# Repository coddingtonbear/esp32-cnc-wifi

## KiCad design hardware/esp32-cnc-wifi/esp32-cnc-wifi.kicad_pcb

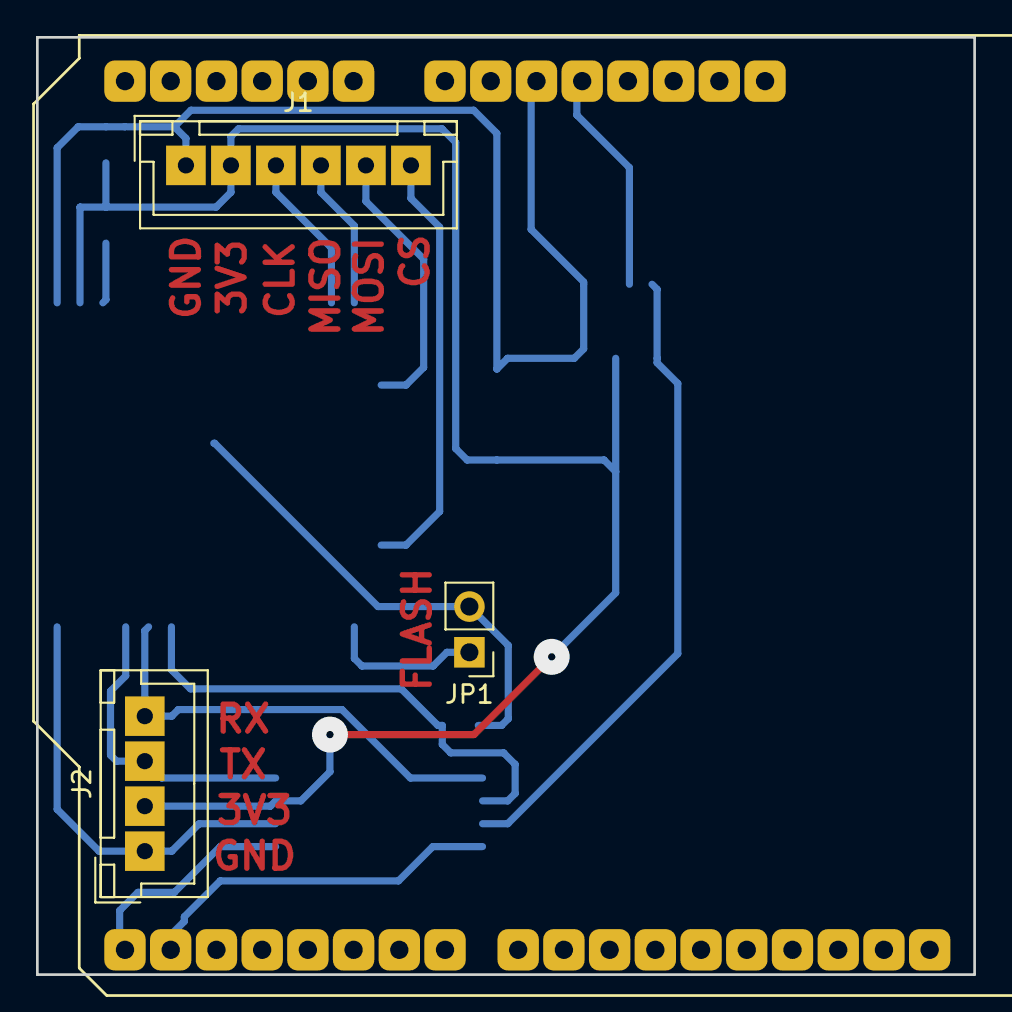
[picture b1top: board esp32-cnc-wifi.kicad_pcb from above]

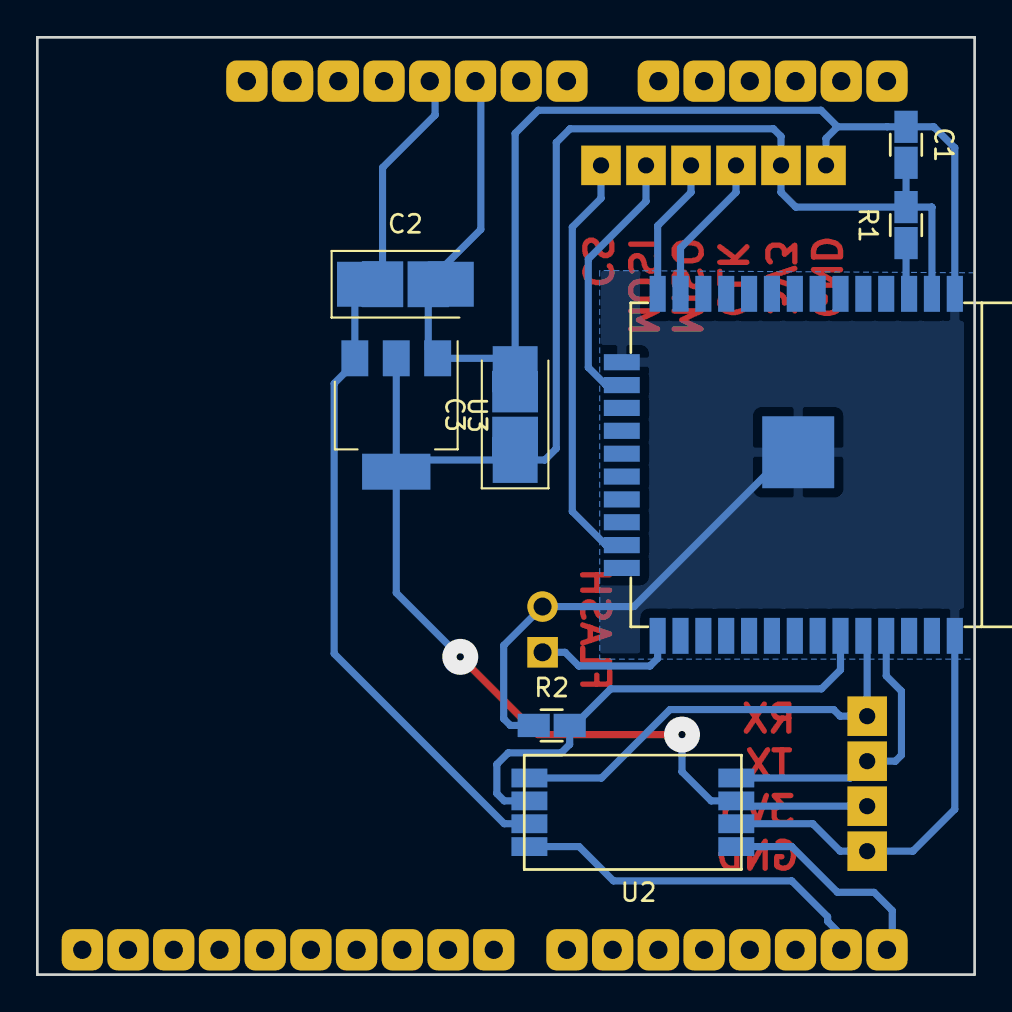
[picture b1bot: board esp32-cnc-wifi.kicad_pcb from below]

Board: 2 copper layers, 52.1 x 52.1 mm, 12 parts (8 on the bottom side), 14 nets.

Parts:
C1: 0.1u; 0805_Milling
C2, C3: 1u; CP_Tantalum_Case-C_EIA-6032-28_Milling
J1: HSPI; JST_XH_B06B-XH-A_06x2.50mm_Straight_LargePads
J2: Prog; JST_XH_B04B-XH-A_04x2.50mm_Straight_LargePads
JP1: Jumper; Pin_Header_Straight_1x02_Pitch2.54mm
R1, R2: 10k; 0805_Milling
U1: ESP-32S; ESP-WROOM-32
U2: TXS0102-DIL; SSOP8-1.27MM-CASTELLATED
U3: AP1117-15; SOT-223-3_TabPin2
XA1: Arduino_Uno_Shield; Arduino_Uno_Shield_LargePads

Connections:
+3V3: C1.2, C3.1, J1.2, J2.2, R1.2, U1.2, U2.3, U3.2
+5V: C2.1, U2.7, U3.3, XA1.5V1
ARDUINO_RX: U2.1, XA1.D0
ARDUINO_TX: U2.8, XA1.D1
ESP_RX: J2.4, U1.34, U2.5
ESP_TX: J2.3, U1.35, U2.4
GND: C1.1, C2.2, C3.2, J1.1, J2.1, JP1.2, R2.1, U1.1, U1.15, U1.38, U1.39, U2.2, U3.1, XA1.GND2
unnamed: J1.3, U1.13
unnamed: J1.4, U1.14
unnamed: J1.5, U1.16
unnamed: J1.6, U1.23
unnamed: JP1.1, U1.25
unnamed: R1.1, U1.3
unnamed: R2.2, U1.33, U2.6

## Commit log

2018-05-04 And so it begins.
2018-05-04 Rotating board by 90-degrees.
2018-05-21 Arduino implementation.
2018-05-30 Adding working software.
